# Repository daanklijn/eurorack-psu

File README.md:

# eurorack-psu

Based on the MFOS design and the [redesign](https://github.com/xavpaice/MFOS-wallwart) made by xavpaice.

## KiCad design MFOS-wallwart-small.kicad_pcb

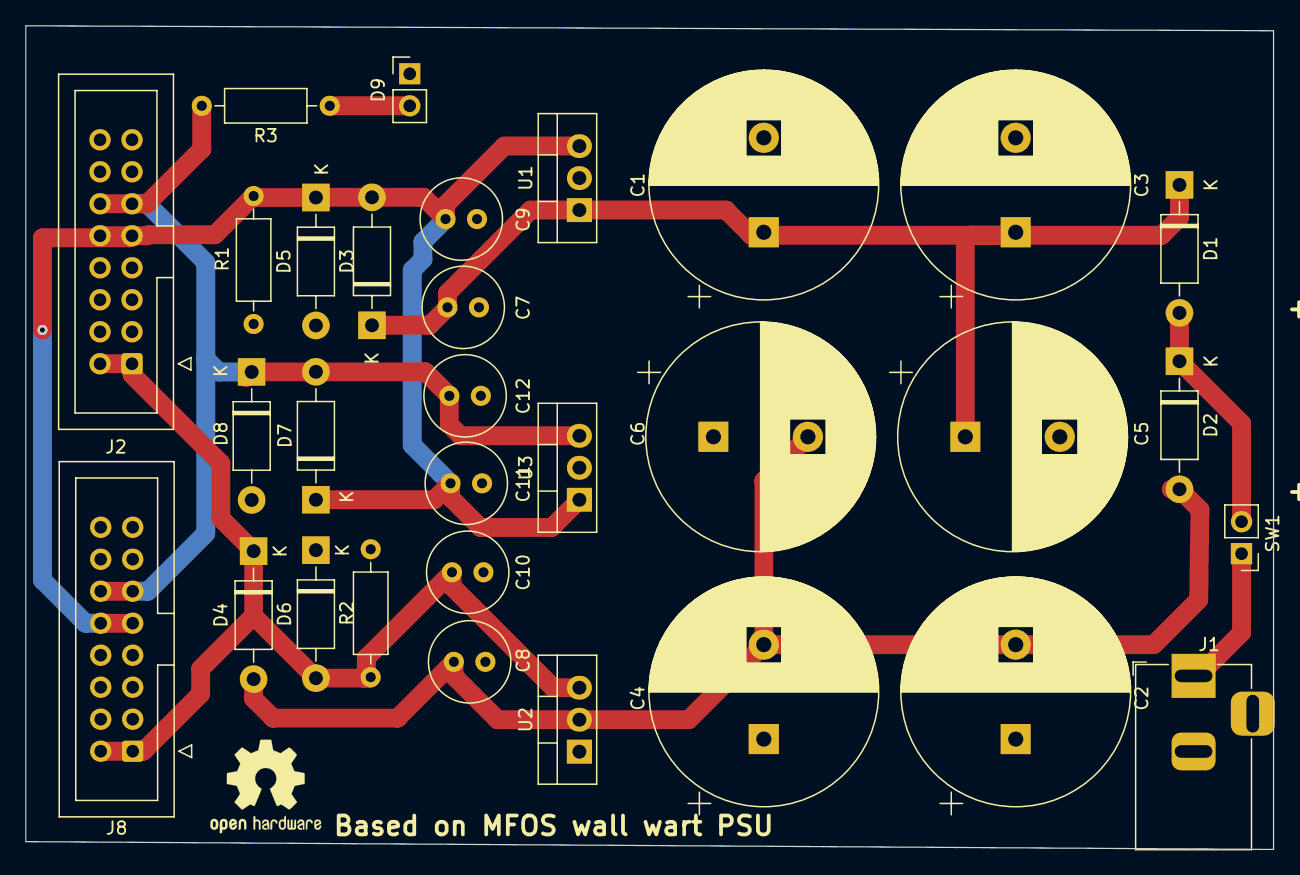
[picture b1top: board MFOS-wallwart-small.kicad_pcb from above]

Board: 2 copper layers, 99.1 x 65.4 mm, 31 parts (0 on the bottom side), 9 nets.

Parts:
C1, C2, C3, C4, C5, C6: 3300uF; CP_Radial_D18.0mm_P7.50mm
C7, C8, C9, C10, C11, C12: 1uF; C_Radial_D6.3mm_H5.0mm_P2.50mm
D1, D2, D3, D4, D5, D6, D7, D8: 1N4004; D_DO-41_SOD81_P10.16mm_Horizontal
D9: LED; PinHeader_1x02_P2.54mm_Vertical
J1: Barrel_Jack; BarrelJack_Horizontal
J2, J8: Connector_Generic:Conn_02x08_Odd_Even; IDC-Header_2x08_P2.54mm_Vertical
R1, R2: 3K3; R_Axial_DIN0207_L6.3mm_D2.5mm_P10.16mm_Horizontal
R3: 160; R_Axial_DIN0207_L6.3mm_D2.5mm_P10.16mm_Horizontal
SW1: SW_SPST; PinHeader_1x02_P2.54mm_Vertical
U1: L7812; TO-220-3_Vertical
U2: L7912; TO-220-3_Vertical
U3: L7805; TO-220-3_Vertical

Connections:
+5V: C12.1, D7.2, D8.1, J2.11, J2.12, J8.11, J8.12, R3.2, U3.3
+12V: C9.1, C11.2, D3.2, D5.1, D7.1, J2.9, J2.10, J8.9, J8.10, R1.1, U1.3, U3.1
-12V: C10.1, D4.1, D6.2, J2.1, J2.2, J8.1, J8.2, R2.1, U2.3
GND: C1.2, C2.1, C3.2, C4.1, C5.2, C6.1, C7.2, C8.2, C9.2, C10.2, C11.1, C12.2, D5.2, D6.1, D8.2, D9.1, J1.2, J2.3, J2.4, J2.5, J2.6, J2.7, J2.8, J8.3, J8.4, J8.5, J8.6, J8.7, J8.8, R1.2, R2.2, U1.2, U2.1, U3.2
unnamed: C1.1, C3.1, C5.1, C7.1, D1.1, D3.1, U1.1
unnamed: C2.2, C4.2, C6.2, C8.1, D2.2, D4.2, U2.2
unnamed: D1.2, D2.1, SW1.2
unnamed: D9.2, R3.1
unnamed: J1.1, SW1.1

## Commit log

2021-07-16 upload files
